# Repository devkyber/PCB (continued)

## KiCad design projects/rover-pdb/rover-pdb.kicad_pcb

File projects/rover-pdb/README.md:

# Rover PDB: start here

The owner closed Rover work on 2026-10-07. This is the sole retained Rover
project. Cleanup preserved its native CAD and current manufacturing-preview
files byte-for-byte. Earlier development checks below retain their dated scope;
closing development does not create a fabrication sign-off.

Open [rover-pdb.kicad_pro](rover-pdb.kicad_pro) in KiCad. The saved seven-sheet
[schematic](rover-pdb.kicad_sch) and [PCB](rover-pdb.kicad_pcb) are the current
owner-editable design. **PCB P5 / circuit A10 with owner edits and L3 stock substitution, 2026-10-05**, retains the owner's
**77.5 × 100 mm** outline, two copper layers / 1 oz, four M3 holes, surface
wire pads and the saved placement, except small L3/TP4 clearance adjustments. The switch choice is deferred. All seven
schematic files preserve owner circuitry, including F1 removal and the added
J8/R6 servo channel. L3 remains 3.3 uH with a new MPN and matching footprint. P2/P3 remain 12 V for the owner's future expansion plans.

**The reviewed updates are applied.** P5 adds two female-socket 3D models,
widens six battery-path segments and adds 48 useful, tented vias beside solid
wire pads and converter grounds. A10 removes F1 and bridges the input to RS1;
there is no onboard battery fuse. P4's separate wide 5 V force connection,
labels, mounting keepouts and manual Pico-fitting metadata are retained.
Motor-energy handling, final switch choice, physical fit and prototype
measurements remain open; this is not a fabrication release. See the
[current verification](docs/review/PCB_VERIFICATION.md).

The 18 V Jetson / independent 12 V comparison was retired at the owner's
request. It and the superseded A3 teaching guide are recoverable from
`C:/Users/tae06/.codex/archives/pcb/cleanup-20261007/PCB.zip`.

- [Schematic PDF, A10](output/pdf/rover-pdb-schematic-A10.pdf)
- [Current PCB assembly and copper PDF, P5](output/pdf/rover-pdb-pcb-review.pdf)
- [Current 3D assembly view](output/review/assembly-3d.png)
- [Schematic BOM](output/schematic-bom.csv) and [purchase notes](docs/design/BOM_NOTES.md)
- [Pipeline walkthrough and provenance](docs/review/PIPELINE_AUDIT.md)

The PCB PDF is regenerated from current CAD and its manifest records source
hashes. The schematic PDF is an A10 review snapshot. Later manual CAD edits can
make either export stale; edit the native files, never an exported drawing.
Native tracks/vias are editable. Routing classes are defaults for new copper,
not automatic resizing or proof of current capacity.

P5 passes native schematic/PCB parity and placement, with **0 DRC errors,
0 warnings and 0 unconnected items** after refill. All **19/19** checked power
paths remain connected when thin power-net tracks are removed in a disposable
fault test. This detects dependence on sense-size copper, not ampacity.
F1 removal combines the two historical fuse connections into one direct input
connection; the P4 control passes 20/20. All 482 native tracks and 167
vias are unlocked. The four bottom-edge connector
pin legends are printed on the back at 1 mm height; the PDF's back view is
viewed from underneath, so those labels read correctly.

## What stays at the root

| Files | Why they are necessary |
| --- | --- |
| `.kicad_pro`, `.kicad_pcb`, root and child `.kicad_sch` | KiCad's editable project and design |
| `project.yaml`, `netmap.json`, `review-profile.yaml` | Pipeline configuration, connectivity contract and human review requirements |
| `REQUIREMENTS.md`, `DESIGN_BASIS.md`, `REFERENCE_REVIEW.md`, `DEVIATIONS.md` | Declared engineering inputs read by the shared pipeline |
| `fp-lib-table`, `sym-lib-table`; `libs/`, `symbols/`, `footprints/` | Self-contained symbols, real pad geometry and 3D models |
| `evidence/` | Exact manufacturer/supplier sources and provenance |
| `AGENTS.md`, `SCHEMATIC_OWNER` | Scope and owner-edit preservation instructions |
| `schematic-intent.yaml` | Historical comparison/generation input, not authority over saved CAD |
| `check_schematic.py` | Extra Rover-specific pin-map and adopted-circuit assertions |

## Open the detail only when needed

| Folder / document | Purpose |
| --- | --- |
| [Current design basis](DESIGN_BASIS.md) | Adopted component choices and electrical calculations |
| [Power controls](docs/design/POWER_DECISIONS.md) | USB-only Pico and VIN-derived motor-enable behavior |
| [12 V / 5 V filters](docs/design/OUTPUT_FILTER_SELECTION.md), [motor filter](docs/design/MOTOR_FILTER_SELECTION.md) | Capacitor/inductor decisions and derating evidence |
| [PCB design](docs/design/PCB_DESIGN.md) | Physical construction, routing defaults, datasheet page map and bench checks |
| [JLCPCB workflow and L3 substitution](docs/design/JLCPCB.md) | Current manufacture files, stock checks, manual KiCad steps and Coilank selection |
| [Schematic review](docs/review/SCHEMATIC_REVIEW.md) | Author checks and unresolved decisions |
| [Footprint review](docs/review/PCB_FOOTPRINT_REVIEW.md), [power layout](docs/review/PCB_POWER_LAYOUT_REVIEW.md), [verification](docs/review/PCB_VERIFICATION.md) | Recorded geometry, physical routing decisions and measured CAD checks |
| `docs/review/records/` | Small original machine reports and owner-review records, with snapshot-specific scope |
| [Layout tools](layout/README.md) | Three read-only audit/export tools; no board-regeneration recipe |
| [Simulations](simulation/README.md) | Actual passive-network results and prepared vendor converter cases; explicit limitations |

## Current circuit in brief

See [the JLCPCB workflow](docs/design/JLCPCB.md) for the current upload package,
stock report and repeatable commands. Older PDF/review links below describe their
named revisions and are not regenerated manufacturing sources.

Three LMR51450 converters supply nominal 12 V, 5 V and 22.19 V. L1/L2/L3 are
6.8/4.7/3.3 µH; RT is open for nominal 500 kHz. The input banks each retain two
10 µF plus 100 nF. Output ceramics are four 22 µF, five 22 µF and four 10 µF,
respectively, with the adopted bulk capacitors. Motor EN comes from the local
VIN-derived switch network and is pulled low with the switch open. Pico is
USB-only; J9 is an optional DNP four-GPIO expansion header. Follow native CAD
and the design basis for exact values and connections.

## Work on this board

Read [AGENTS.md](AGENTS.md) and the [shared workflow](../../docs/WORKFLOW.md).
Save and close KiCad before assisted writes. Start each candidate from current
saved CAD; preview and inspect it before applying. An older generation recipe
must never restore older routing or component values over owner edits.

```powershell
uv run python projects/rover-pdb/check_schematic.py
uv run pcb-copilot research projects/rover-pdb --verify
uv run pcb-copilot review projects/rover-pdb
uv run pcb-copilot clean projects/rover-pdb
```

`clean` is a preview unless `--apply` is supplied; it removes only named,
reproducible preview files. It does not remove the folders of useful documents
above. The deep 2026-10-01 cleanup archived historical drafts/recovery copies
outside the repo before removal. Its backup and retention policy are recorded
in the [architecture guide](../../docs/ARCHITECTURE.md#cleanup-and-retention).

This is the baseline Rover project. On 2026-10-01 it was renamed from
`rover-pdb-readable`, preserving the owner's saved CAD bytes. The earlier
LM73606 comparison project was moved intact outside the repository to
`C:/Users/tae06/.codex/archives/pcb/rover-consolidation-20261001-114628/original-rover/`.
Historical reports and the teaching guide retain their former project names;
they are records of earlier revisions, not alternate current designs.

Current CAD checks do not establish motor-regeneration handling, thermal/load-step behavior,
assembly fit or harness protection. Five project decisions plus the two shared
human release decisions remain required; only `pcb-copilot release` creates
manufacturing output. The retained upload preview remains a dated snapshot.

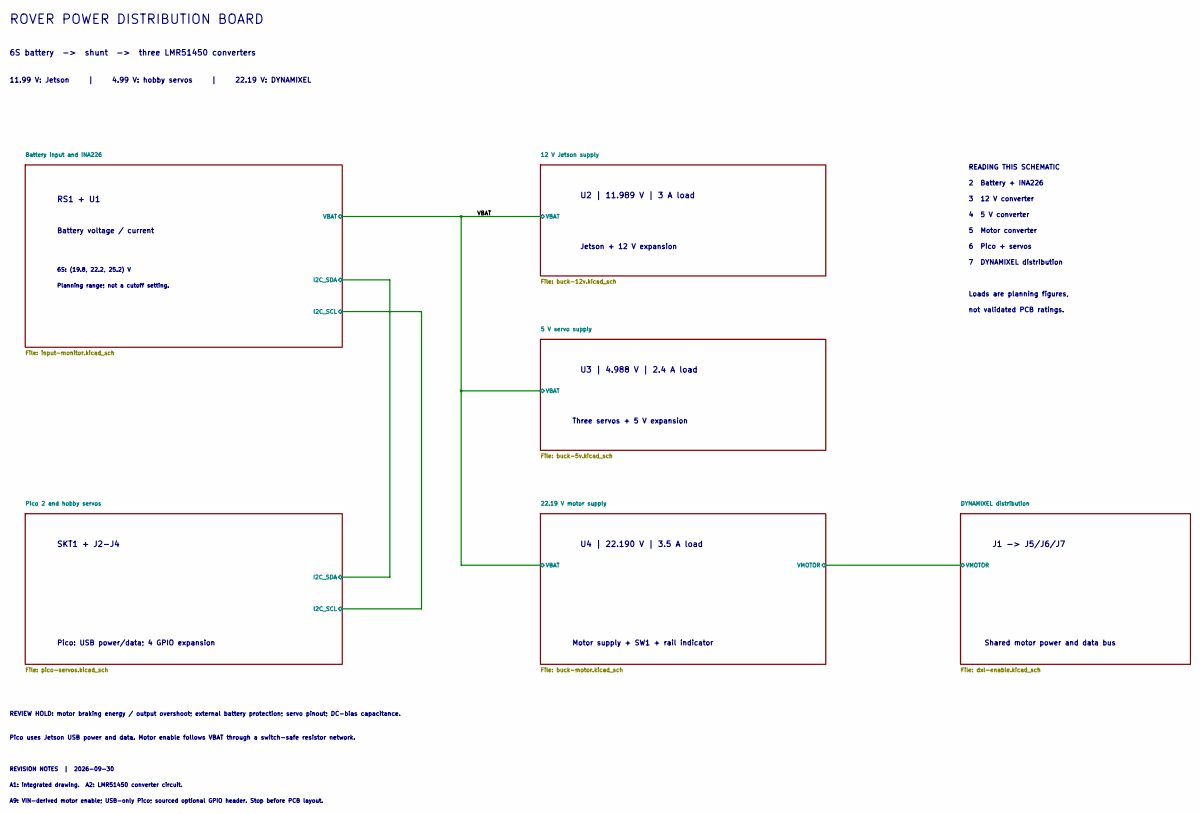
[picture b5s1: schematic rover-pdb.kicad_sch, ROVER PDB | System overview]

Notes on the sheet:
ROVER POWER DISTRIBUTION BOARD
3 12 V converter
RS1 + U1
Planning range; not a cutoff setting.
REVISION NOTES | 2026-09-30
U4 | 22.190 V | 3.5 A load
U2 | 11.989 V | 3 A load
Loads are planning figures,
Jetson + 12 V expansion
A9: VIN-derived motor enable; USB-only Pico; sourced optional GPIO header. Stop before PCB layout.
U3 | 4.988 V | 2.4 A load
not validated PCB ratings.
SKT1 + J2-J4
5 Motor converter
11.99 V: Jetson | 4.99 V: hobby servos | 22.19 V: DYNAMIXEL
Motor supply + SW1 + rail indicator
Pico: USB power/data; 4 GPIO expansion
2 Battery + INA226
Shared motor power and data bus
A1: integrated drawing. A2: LMR51450 converter circuit.
6 Pico + servos
Three servos + 5 V expansion
REVIEW HOLD: motor braking energy / output overshoot; external battery protection; servo pinout; DC-bias capacitance.
READING THIS SCHEMATIC
Battery voltage / current
J1 -> J5/J6/J7
6S: (19.8, 22.2, 25.2) V
Pico uses Jetson USB power and data. Motor enable follows VBAT through a switch-safe resistor network.
4 5 V converter
7 DYNAMIXEL distribution
6S battery -> shunt -> three LMR51450 converters

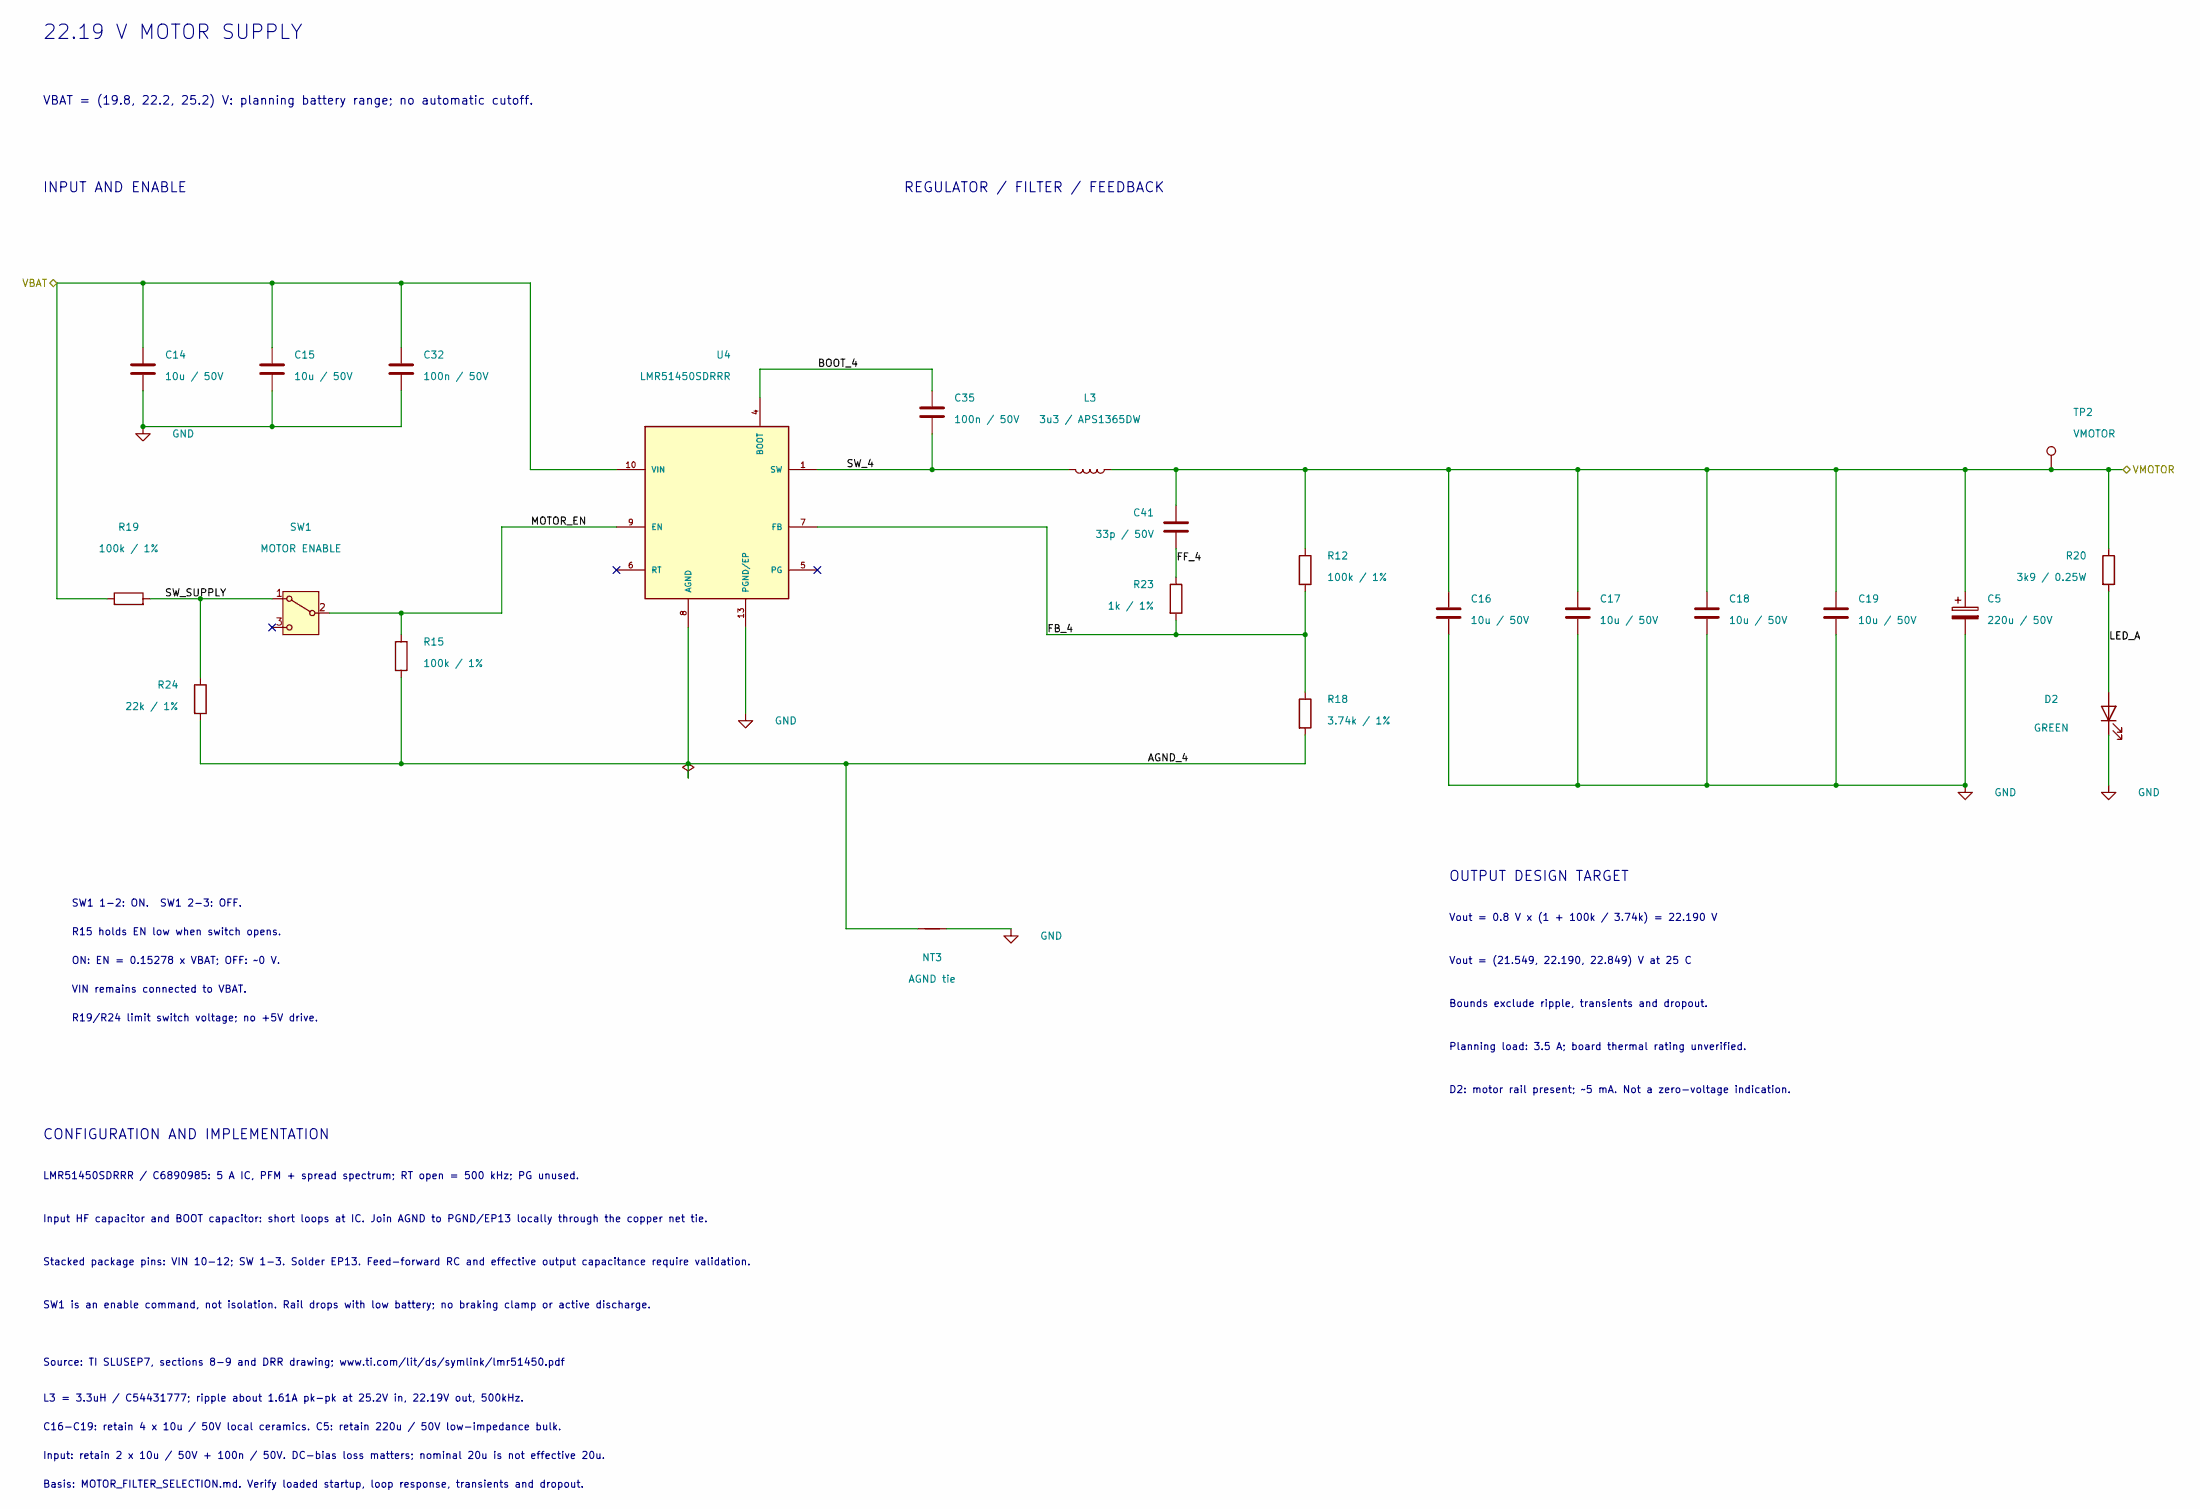
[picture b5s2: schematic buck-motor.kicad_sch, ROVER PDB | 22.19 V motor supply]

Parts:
C5: 220u / 50V; CP_Radial_D10.0mm_P5.00mm; MPN EEU-FR1H221B; LCSC Part C1579630
C14, C15, C16, C17, C18, C19: 10u / 50V; C_1210_3225Metric; MPN GRM32ER71H106KA12L; LCSC Part C77102
C32, C35: 100n / 50V; C_0805_2012Metric; MPN CL21B104KBCNNNC; LCSC Part C1711
C41: 33p / 50V; C_0603_1608Metric; MPN CL10C330JB8NNNC; LCSC Part C1663
D2: GREEN; KT0805G_0805_A1_K2; MPN KT-0805G; LCSC Part C2297
L3: 3u3 / APS1365DW; APS1365DW_13.8x12.6_P11.5; MPN APS1365M3R3DW; LCSC Part C54431777
NT3: AGND tie; AGND_Tie_LMR51450
R12, R15, R19: 100k / 1%; R_0805_2012Metric; MPN RC0805FR-07100KL; LCSC Part C96346
R18: 3.74k / 1%; R_0805_2012Metric; MPN 0805W8F3741T5E; LCSC Part C65649
R20: 3k9 / 0.25W; R_1206_3216Metric; MPN RC1206FR-073K9L; LCSC Part C137289
R23: 1k / 1%; R_0805_2012Metric; MPN 0805W8F1001T5E; LCSC Part C17513
R24: 22k / 1%; R_0805_2012Metric; MPN 0805W8F2202T5E; LCSC Part C17560
SW1: MOTOR ENABLE; SW_Slide_SPDT_Angled_CK_OS102011MA1Q; MPN OS102011MA1QN1; LCSC Part C226259
TP2: VMOTOR; TestPoint_Pad_D2.0mm; MPN VMOTOR
U4: LMR51450SDRRR; LMR51450_DRR_WSON12_3x3; MPN LMR51450SDRRR; LCSC Part C6890985

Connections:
/22.19 V motor supply/AGND_4: NT3.1, R15.2, R18.2, R24.2, U4.8 (AGND)
/22.19 V motor supply/BOOT_4: C35.1, U4.4 (BOOT)
/22.19 V motor supply/FB_4: R12.2, R18.1, R23.2, U4.7 (FB)
/22.19 V motor supply/FF_4: C41.2, R23.1
/22.19 V motor supply/LED_A: D2.1 (A), R20.2
/22.19 V motor supply/MOTOR_EN: R15.1, SW1.2 (B), U4.9 (EN)
/22.19 V motor supply/SW_4: C35.2, L3.2, U4.1 (SW), U4.2 (SW), U4.3 (SW)
/22.19 V motor supply/SW_SUPPLY: R19.2, R24.1, SW1.1 (A)
/22.19 V motor supply/VMOTOR: C5.1, C16.1, C17.1, C18.1, C19.1, C41.1, L3.1, R12.1, R20.1, TP2.1 (1_1); also elsewhere on the board
/VBAT: C14.1, C15.1, C32.1, R19.1, U4.10 (VIN), U4.11 (VIN), U4.12 (VIN); also elsewhere on the board
GND: C5.2, C14.2, C15.2, C16.2, C17.2, C18.2, C19.2, C32.2, D2.2 (K), NT3.2, U4.13 (PGND/EP); also elsewhere on the board

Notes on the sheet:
Vout = 0.8 V x (1 + 100k / 3.74k) = 22.190 V
REGULATOR / FILTER / FEEDBACK
Basis: MOTOR_FILTER_SELECTION.md. Verify loaded startup, loop response, transients and dropout.
LMR51450SDRRR / C6890985: 5 A IC, PFM + spread spectrum; RT open = 500 kHz; PG unused.
Input HF capacitor and BOOT capacitor: short loops at IC. Join AGND to PGND/EP13 locally through the copper net tie.
ON: EN = 0.15278 x VBAT; OFF: ~0 V.
22.19 V MOTOR SUPPLY
OUTPUT DESIGN TARGET
SW1 is an enable command, not isolation. Rail drops with low battery; no braking clamp or active discharge.
D2: motor rail present; ~5 mA. Not a zero-voltage indication.
CONFIGURATION AND IMPLEMENTATION
Input: retain 2 x 10u / 50V + 100n / 50V. DC-bias loss matters; nominal 20u is not effective 20u.
Stacked package pins: VIN 10-12; SW 1-3. Solder EP13. Feed-forward RC and effective output capacitance require validation.
Source: TI SLUSEP7, sections 8-9 and DRR drawing; www.ti.com/lit/ds/symlink/lmr51450.pdf
Planning load: 3.5 A; board thermal rating unverified.
Bounds exclude ripple, transients and dropout.
SW1 1-2: ON. SW1 2-3: OFF.
INPUT AND ENABLE
Vout = (21.549, 22.190, 22.849) V at 25 C
VBAT = (19.8, 22.2, 25.2) V: planning battery range; no automatic cutoff.
R15 holds EN low when switch opens.
L3 = 3.3uH / C54431777; ripple about 1.61A pk-pk at 25.2V in, 22.19V out, 500kHz.
VIN remains connected to VBAT.
R19/R24 limit switch voltage; no +5V drive.
C16-C19: retain 4 x 10u / 50V local ceramics. C5: retain 220u / 50V low-impedance bulk.

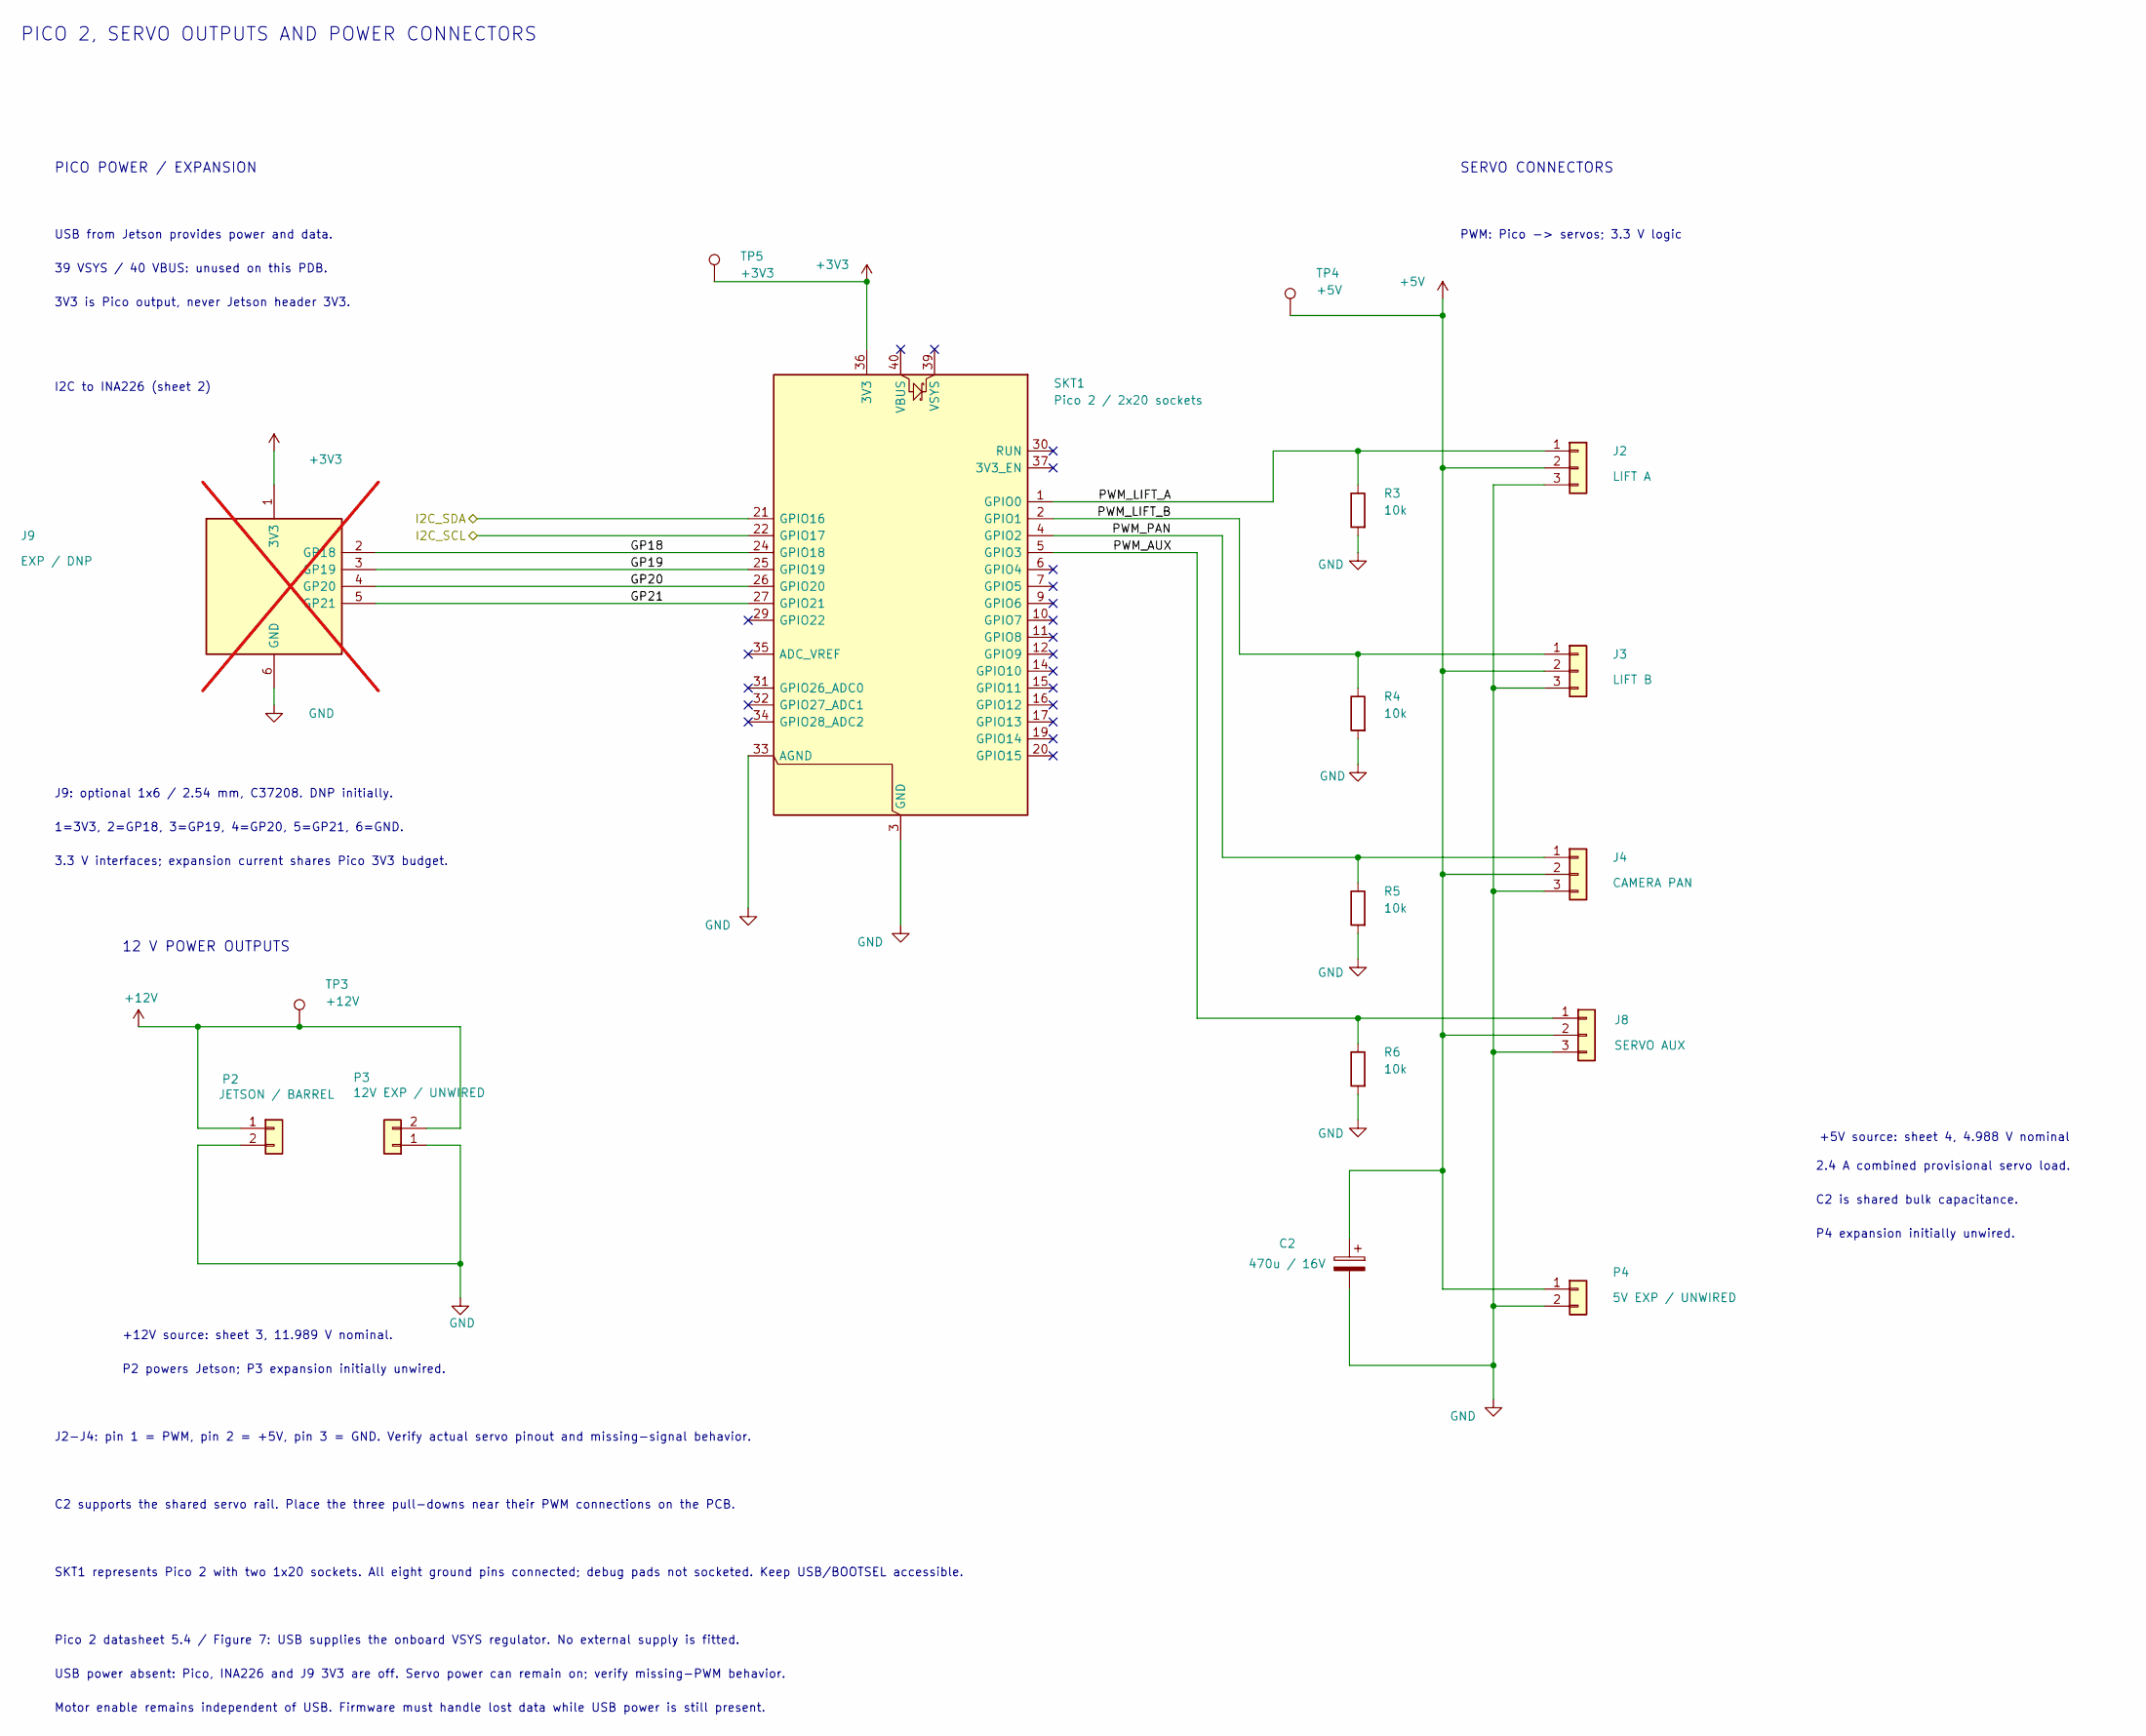
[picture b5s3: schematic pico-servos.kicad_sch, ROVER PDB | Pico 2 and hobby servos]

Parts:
C2: 470u / 16V; CP_Radial_D8.0mm_P5.00mm; MPN EEU-FR1C471B; LCSC Part C1579437
J2: LIFT A; PinHeader_1x03_P2.54mm_Vertical; MPN TSW-103-07-G-S; LCSC Part C3335811
J3: LIFT B; PinHeader_1x03_P2.54mm_Vertical; MPN TSW-103-07-G-S; LCSC Part C3335811
J4: CAMERA PAN; PinHeader_1x03_P2.54mm_Vertical; MPN TSW-103-07-G-S; LCSC Part C3335811
J8: SERVO AUX; PinHeader_1x03_P2.54mm_Vertical; MPN TSW-103-07-G-S; LCSC Part C3335811
J9: EXP / DNP; PinHeader_1x06_P2.54mm_Vertical; MPN 2.54-1x6P直针; LCSC Part C37208; not fitted
P2: JETSON / BARREL; WirePads_2_5x6_P9; MPN JETSON / BARREL
P3: 12V EXP / UNWIRED; WirePads_2_5x6_P9; MPN 12V EXP / UNWIRED
P4: 5V EXP / UNWIRED; WirePads_2_5x6_P9; MPN 5V EXP / UNWIRED
R3, R4, R5, R6: 10k; R_0805_2012Metric; MPN RC0805FR-0710KL; LCSC Part C84376
SKT1: Pico 2 / 2x20 sockets; Pico2_Sockets_LXWCONN_254PM_1x20; MPN Pico 2
TP3: +12V; TestPoint_Pad_D2.0mm; MPN +12V
TP4: +5V; TestPoint_Pad_D2.0mm; MPN +5V
TP5: +3V3; TestPoint_Pad_D2.0mm; MPN +3V3

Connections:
+3V3: J9.1 (3V3), SKT1.36 (3V3), TP5.1 (1_1); also elsewhere on the board
+5V: C2.1, J2.2, J3.2, J4.2, J8.2, P4.1, TP4.1 (1_1); also elsewhere on the board
+12V: P2.1, P3.2, TP3.1 (1_1); also elsewhere on the board
/Battery input and INA226/I2C_SCL: SKT1.22 (GPIO17); also elsewhere on the board
/Battery input and INA226/I2C_SDA: SKT1.21 (GPIO16); also elsewhere on the board
/Pico 2 and hobby servos/GP18: J9.2 (GP18), SKT1.24 (GPIO18)
/Pico 2 and hobby servos/GP19: J9.3 (GP19), SKT1.25 (GPIO19)
/Pico 2 and hobby servos/GP20: J9.4 (GP20), SKT1.26 (GPIO20)
/Pico 2 and hobby servos/GP21: J9.5 (GP21), SKT1.27 (GPIO21)
/Pico 2 and hobby servos/PWM_AUX: J8.1, R6.1, SKT1.5 (GPIO3)
/Pico 2 and hobby servos/PWM_LIFT_A: J2.1, R3.1, SKT1.1 (GPIO0)
/Pico 2 and hobby servos/PWM_LIFT_B: J3.1, R4.1, SKT1.2 (GPIO1)
/Pico 2 and hobby servos/PWM_PAN: J4.1, R5.1, SKT1.4 (GPIO2)
GND: C2.2, J2.3, J3.3, J4.3, J8.3, J9.6 (GND), P2.2, P3.1, P4.2, R3.2, R4.2, R5.2, R6.2, SKT1.3 (GND), SKT1.8 (GND), SKT1.13 (GND), SKT1.18 (GND), SKT1.23 (GND), SKT1.28 (GND), SKT1.33 (AGND), SKT1.38 (GND); also elsewhere on the board

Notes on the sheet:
PWM: Pico -> servos; 3.3 V logic
SERVO CONNECTORS
1=3V3, 2=GP18, 3=GP19, 4=GP20, 5=GP21, 6=GND.
USB from Jetson provides power and data.
I2C to INA226 (sheet 2)
12 V POWER OUTPUTS
C2 is shared bulk capacitance.
P2 powers Jetson; P3 expansion initially unwired.
+12V source: sheet 3, 11.989 V nominal.
+5V source: sheet 4, 4.988 V nominal
C2 supports the shared servo rail. Place the three pull-downs near their PWM connections on the PCB.
3V3 is Pico output, never Jetson header 3V3.
Motor enable remains independent of USB. Firmware must handle lost data while USB power is still present.
PICO 2, SERVO OUTPUTS AND POWER CONNECTORS
J2-J4: pin 1 = PWM, pin 2 = +5V, pin 3 = GND. Verify actual servo pinout and missing-signal behavior.
USB power absent: Pico, INA226 and J9 3V3 are off. Servo power can remain on; verify missing-PWM behavior.
P4 expansion initially unwired.
SKT1 represents Pico 2 with two 1x20 sockets. All eight ground pins connected; debug pads not socketed. Keep USB/BOOTSEL accessible.
3.3 V interfaces; expansion current shares Pico 3V3 budget.
2.4 A combined provisional servo load.
PICO POWER / EXPANSION
J9: optional 1x6 / 2.54 mm, C37208. DNP initially.
Pico 2 datasheet 5.4 / Figure 7: USB supplies the onboard VSYS regulator. No external supply is fitted.
39 VSYS / 40 VBUS: unused on this PDB.

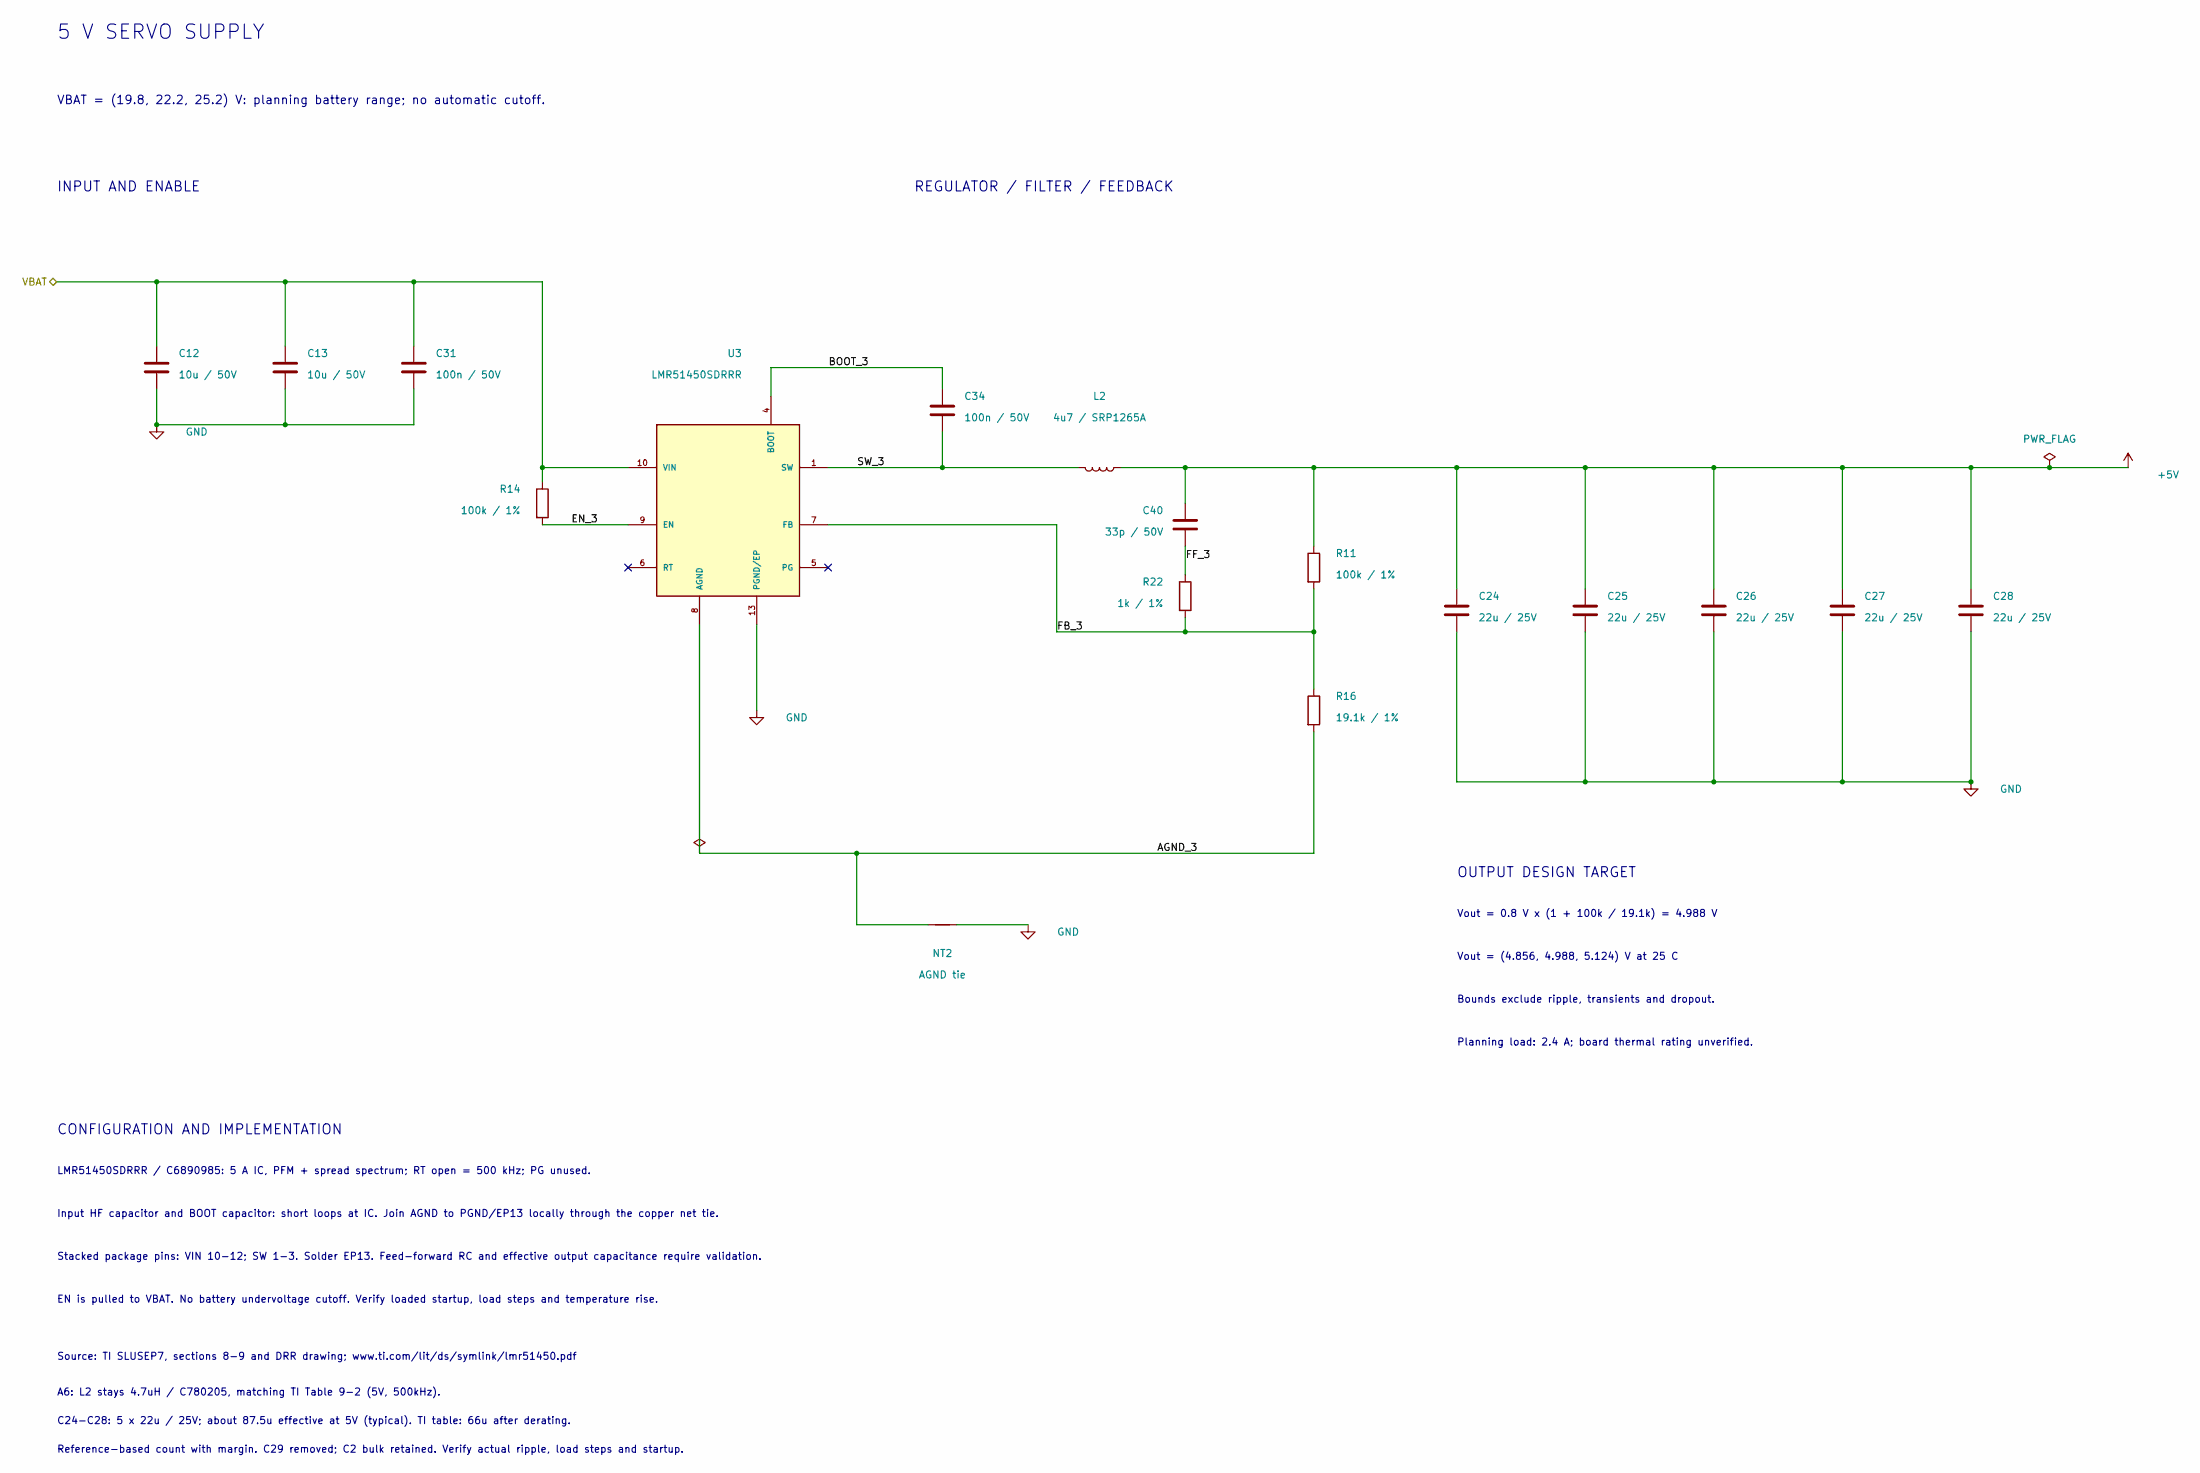
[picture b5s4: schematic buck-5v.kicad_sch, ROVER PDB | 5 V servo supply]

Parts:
C12, C13: 10u / 50V; C_1210_3225Metric; MPN GRM32ER71H106KA12L; LCSC Part C77102
C24, C25, C26, C27, C28: 22u / 25V; C_1210_3225Metric; MPN CL32B226KAJNNNE; LCSC Part C309062
C31, C34: 100n / 50V; C_0805_2012Metric; MPN CL21B104KBCNNNC; LCSC Part C1711
C40: 33p / 50V; C_0603_1608Metric; MPN CL10C330JB8NNNC; LCSC Part C1663
L2: 4u7 / SRP1265A; SRP1265A_LeadFrame_13.5x12.5_P11.1; MPN SRP1265A-4R7M; LCSC Part C780205
NT2: AGND tie; AGND_Tie_LMR51450
R11, R14: 100k / 1%; R_0805_2012Metric; MPN RC0805FR-07100KL; LCSC Part C96346
R16: 19.1k / 1%; R_0805_2012Metric; MPN 0805W8F1912T5E; LCSC Part C17508
R22: 1k / 1%; R_0805_2012Metric; MPN 0805W8F1001T5E; LCSC Part C17513
U3: LMR51450SDRRR; LMR51450_DRR_WSON12_3x3; MPN LMR51450SDRRR; LCSC Part C6890985

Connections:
+5V: C24.1, C25.1, C26.1, C27.1, C28.1, C40.1, L2.1, R11.1; also elsewhere on the board
/5 V servo supply/AGND_3: NT2.1, R16.2, U3.8 (AGND)
/5 V servo supply/BOOT_3: C34.1, U3.4 (BOOT)
/5 V servo supply/EN_3: R14.2, U3.9 (EN)
/5 V servo supply/FB_3: R11.2, R16.1, R22.2, U3.7 (FB)
/5 V servo supply/FF_3: C40.2, R22.1
/5 V servo supply/SW_3: C34.2, L2.2, U3.1 (SW), U3.2 (SW), U3.3 (SW)
/VBAT: C12.1, C13.1, C31.1, R14.1, U3.10 (VIN), U3.11 (VIN), U3.12 (VIN); also elsewhere on the board
GND: C12.2, C13.2, C24.2, C25.2, C26.2, C27.2, C28.2, C31.2, NT2.2, U3.13 (PGND/EP); also elsewhere on the board

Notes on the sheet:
A6: L2 stays 4.7uH / C780205, matching TI Table 9-2 (5V, 500kHz).
Reference-based count with margin. C29 removed; C2 bulk retained. Verify actual ripple, load steps and startup.
Vout = (4.856, 4.988, 5.124) V at 25 C
VBAT = (19.8, 22.2, 25.2) V: planning battery range; no automatic cutoff.
5 V SERVO SUPPLY
CONFIGURATION AND IMPLEMENTATION
EN is pulled to VBAT. No battery undervoltage cutoff. Verify loaded startup, load steps and temperature rise.
Input HF capacitor and BOOT capacitor: short loops at IC. Join AGND to PGND/EP13 locally through the copper net tie.
Stacked package pins: VIN 10-12; SW 1-3. Solder EP13. Feed-forward RC and effective output capacitance require validation.
INPUT AND ENABLE
Source: TI SLUSEP7, sections 8-9 and DRR drawing; www.ti.com/lit/ds/symlink/lmr51450.pdf
Bounds exclude ripple, transients and dropout.
OUTPUT DESIGN TARGET
C24-C28: 5 x 22u / 25V; about 87.5u effective at 5V (typical). TI table: 66u after derating.
REGULATOR / FILTER / FEEDBACK
LMR51450SDRRR / C6890985: 5 A IC, PFM + spread spectrum; RT open = 500 kHz; PG unused.
Vout = 0.8 V x (1 + 100k / 19.1k) = 4.988 V
Planning load: 2.4 A; board thermal rating unverified.

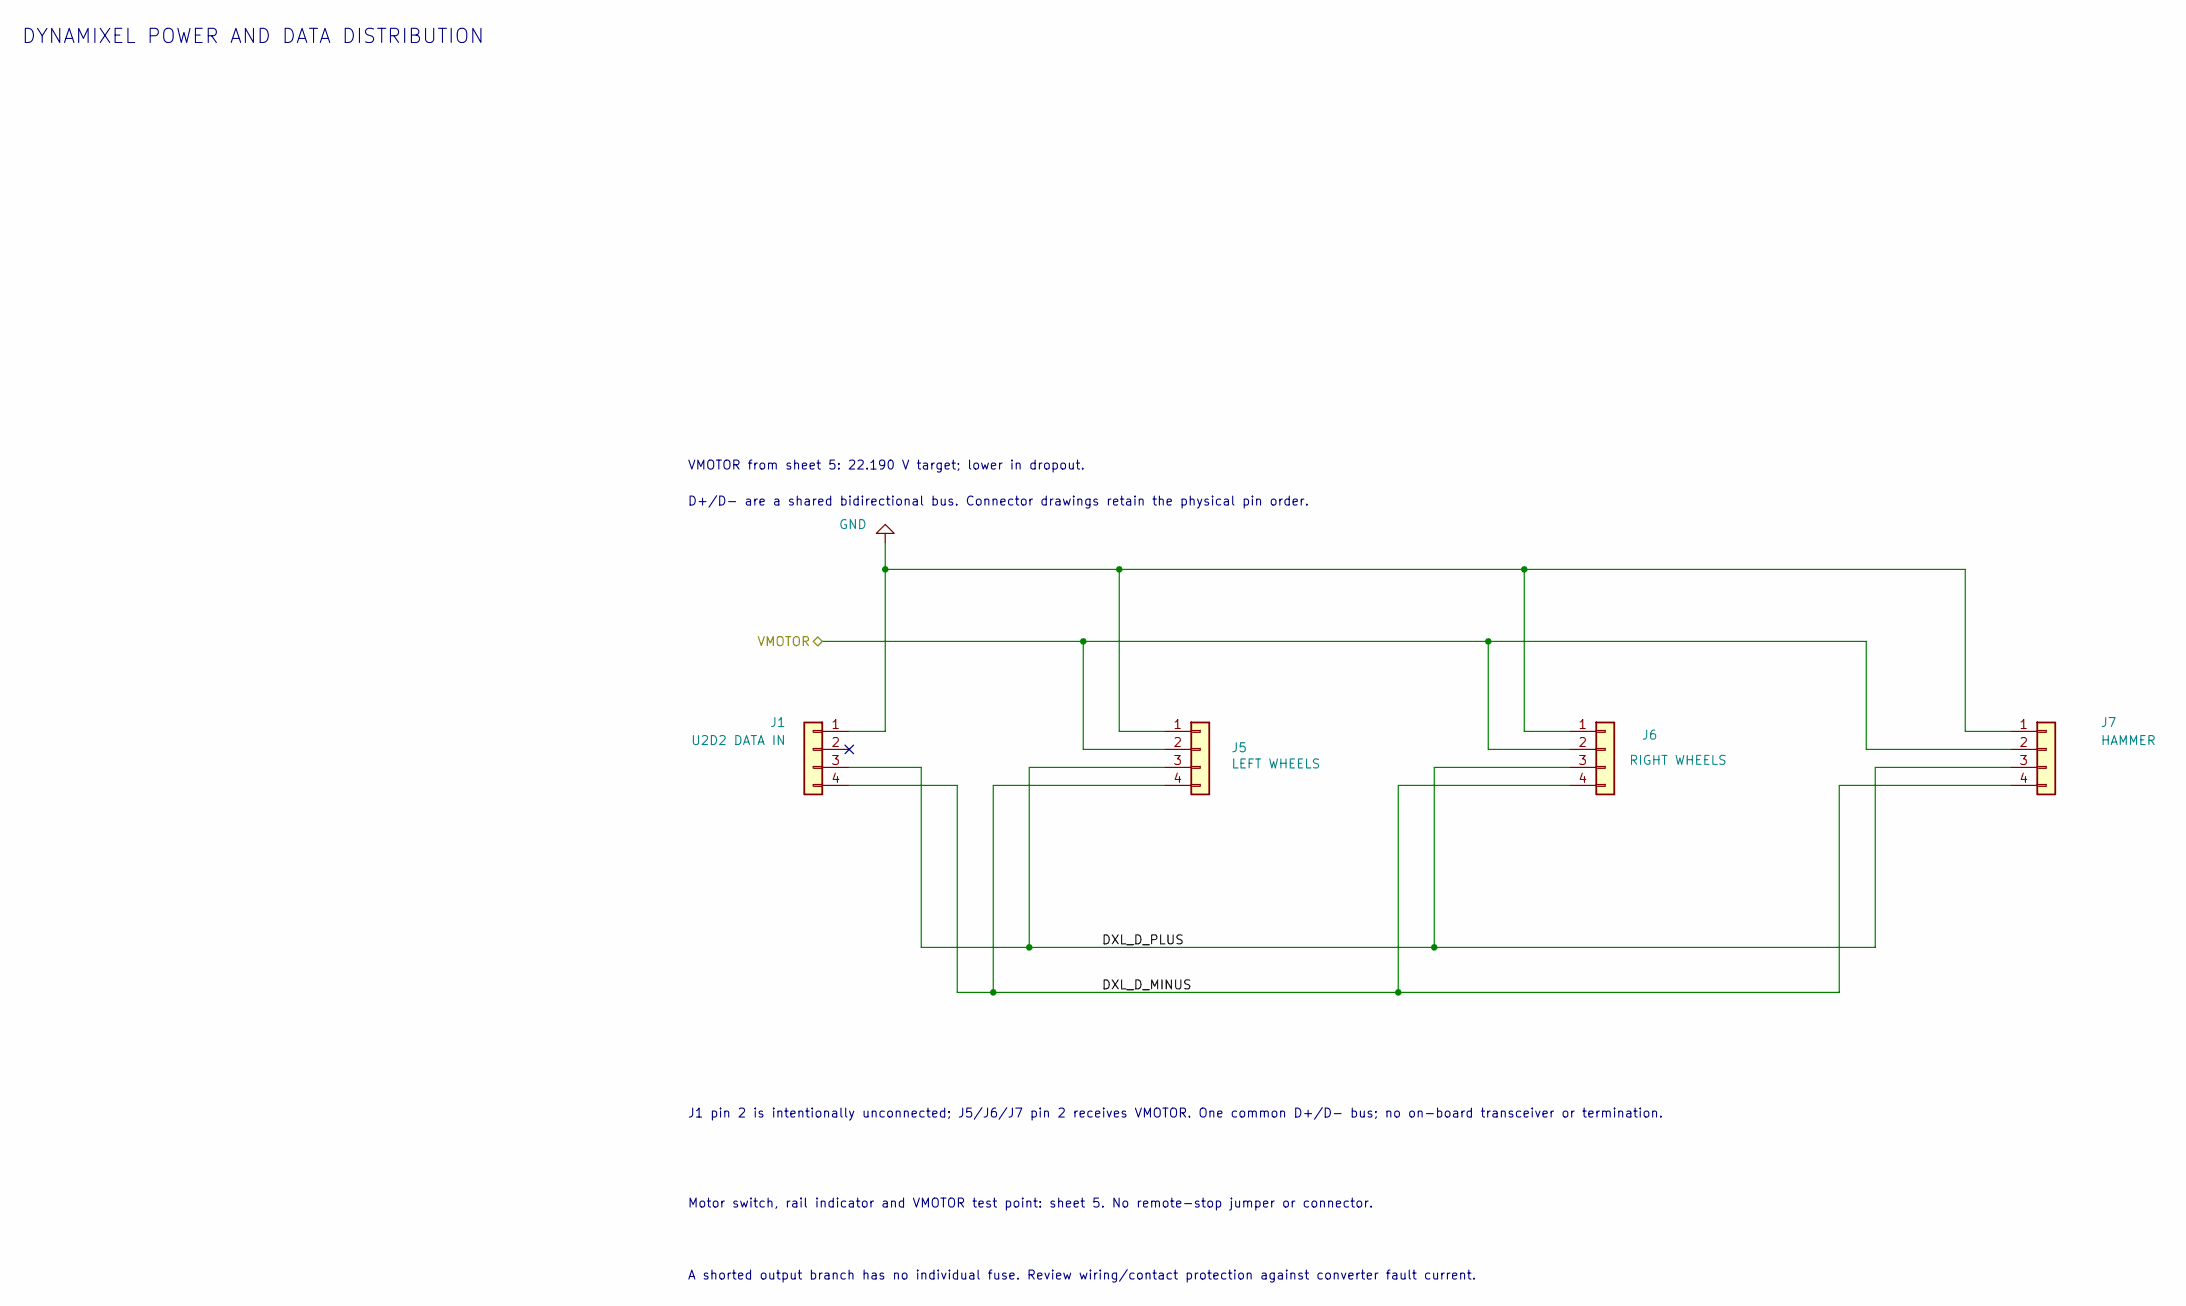
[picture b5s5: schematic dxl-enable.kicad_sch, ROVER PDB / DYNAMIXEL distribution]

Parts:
J1: U2D2 DATA IN; JST_EH_B4B-EH-A_1x04_P2.50mm_Vertical; MPN B4B-EH-A(LF)(SN); LCSC Part C160258
J5: LEFT WHEELS; JST_EH_B4B-EH-A_1x04_P2.50mm_Vertical; MPN B4B-EH-A(LF)(SN); LCSC Part C160258
J6: RIGHT WHEELS; JST_EH_B4B-EH-A_1x04_P2.50mm_Vertical; MPN B4B-EH-A(LF)(SN); LCSC Part C160258
J7: HAMMER; JST_EH_B4B-EH-A_1x04_P2.50mm_Vertical; MPN B4B-EH-A(LF)(SN); LCSC Part C160258

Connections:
/22.19 V motor supply/VMOTOR: J5.2, J6.2, J7.2; also elsewhere on the board
/DYNAMIXEL distribution/DXL_D_MINUS: J1.4, J5.4, J6.4, J7.4
/DYNAMIXEL distribution/DXL_D_PLUS: J1.3, J5.3, J6.3, J7.3
GND: J1.1, J5.1, J6.1, J7.1; also elsewhere on the board

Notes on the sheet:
VMOTOR from sheet 5: 22.190 V target; lower in dropout.
D+/D- are a shared bidirectional bus. Connector drawings retain the physical pin order.
Motor switch, rail indicator and VMOTOR test point: sheet 5. No remote-stop jumper or connector.
DYNAMIXEL POWER AND DATA DISTRIBUTION
J1 pin 2 is intentionally unconnected; J5/J6/J7 pin 2 receives VMOTOR. One common D+/D- bus; no on-board transceiver or termination.
A shorted output branch has no individual fuse. Review wiring/contact protection against converter fault current.
